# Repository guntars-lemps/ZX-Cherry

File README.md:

The ZX Cherry is a keyboard replacement for the ZX Spectrum plus membrane keyboard based on Cherry MX switches. The keyboard keeps the original look of the ZX Spectrum plus which has a much better and more durable keyboard. For extended keys, the BU4066 (or compatible) switches and other elements are used. I suggest to use brown cherry switches, they are noiseless and have tactile feedback.

To use ZX Cherry keyboard together with the original zx spectrum board, the ribbon cable connectors should be replaced with wired connectors, and additionally two power wires must be routed together with the KB0..KB4 wires to JP1 connector

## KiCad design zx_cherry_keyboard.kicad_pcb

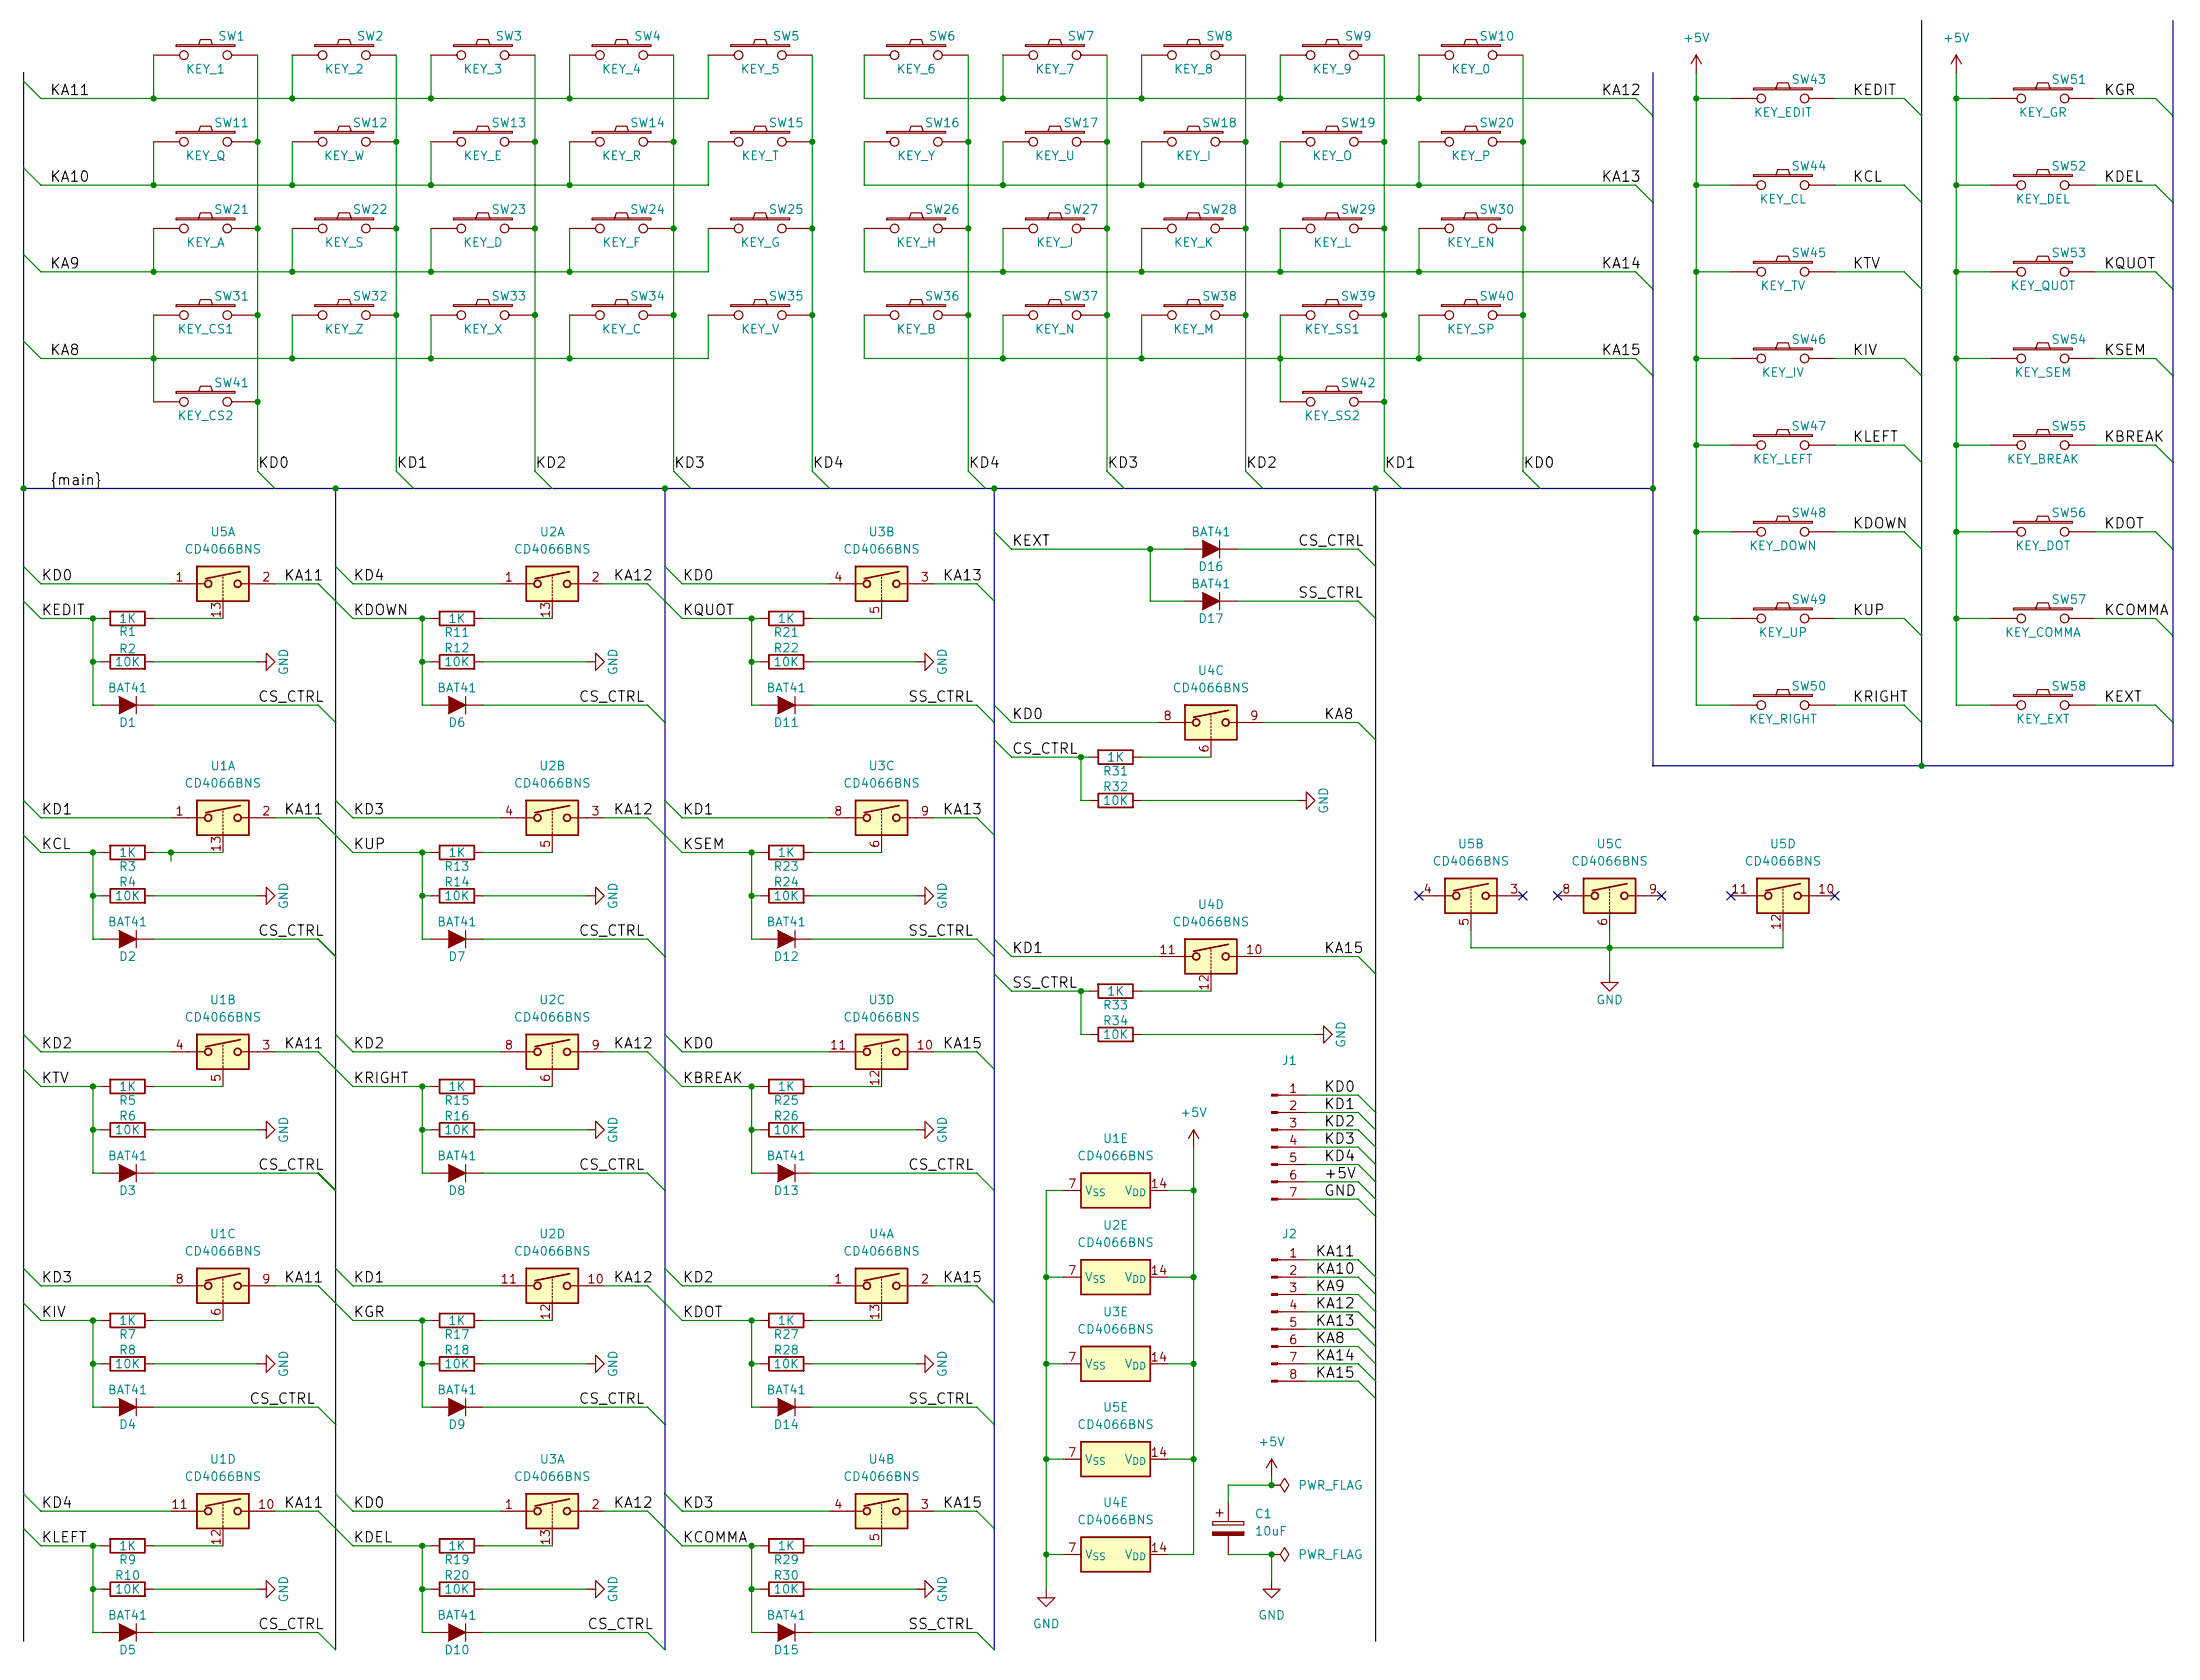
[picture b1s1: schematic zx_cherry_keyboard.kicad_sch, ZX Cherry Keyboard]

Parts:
C1: 10uF; CP_EIA-7343-43_Kemet-X_Pad2.25x2.55mm_HandSolder
D1, D2, D3, D4, D5, D6, D7, D8, D9, D10, D11, D12, D13, D14, D15, D16, D17: BAT41; D_DO-35_SOD27_P12.70mm_Horizontal
J1: Conn_01x07_Pin; PinHeader_1x07_P2.54mm_Horizontal
J2: Conn_01x08_Pin; PinHeader_1x08_P2.54mm_Horizontal
R1, R3, R5, R7, R9, R11, R13, R15, R17, R19, R21, R23, R25, R27, R29, R31, R33: 1K; R_0805_2012Metric_Pad1.20x1.40mm_HandSolder
R2, R4, R6, R8, R10, R12, R14, R16, R18, R20, R22, R24, R26, R28, R30, R32, R34: 10K; R_0805_2012Metric_Pad1.20x1.40mm_HandSolder
SW1: KEY_1; SW_Cherry_MX_1.00u_Plate
SW2: KEY_2; SW_Cherry_MX_1.00u_Plate
SW3: KEY_3; SW_Cherry_MX_1.00u_Plate
SW4: KEY_4; SW_Cherry_MX_1.00u_Plate
SW5: KEY_5; SW_Cherry_MX_1.00u_Plate
SW6: KEY_6; SW_Cherry_MX_1.00u_Plate
SW7: KEY_7; SW_Cherry_MX_1.00u_Plate
SW8: KEY_8; SW_Cherry_MX_1.00u_Plate
SW9: KEY_9; SW_Cherry_MX_1.00u_Plate
SW10: KEY_0; SW_Cherry_MX_1.00u_Plate
SW11: KEY_Q; SW_Cherry_MX_1.00u_Plate
SW12: KEY_W; SW_Cherry_MX_1.00u_Plate
SW13: KEY_E; SW_Cherry_MX_1.00u_Plate
SW14: KEY_R; SW_Cherry_MX_1.00u_Plate
SW15: KEY_T; SW_Cherry_MX_1.00u_Plate
SW16: KEY_Y; SW_Cherry_MX_1.00u_Plate
SW17: KEY_U; SW_Cherry_MX_1.00u_Plate
SW18: KEY_I; SW_Cherry_MX_1.00u_Plate
SW19: KEY_O; SW_Cherry_MX_1.00u_Plate
SW20: KEY_P; SW_Cherry_MX_1.00u_Plate
SW21: KEY_A; SW_Cherry_MX_1.00u_Plate
SW22: KEY_S; SW_Cherry_MX_1.00u_Plate
SW23: KEY_D; SW_Cherry_MX_1.00u_Plate
SW24: KEY_F; SW_Cherry_MX_1.00u_Plate
SW25: KEY_G; SW_Cherry_MX_1.00u_Plate
SW26: KEY_H; SW_Cherry_MX_1.00u_Plate
SW27: KEY_J; SW_Cherry_MX_1.00u_Plate
SW28: KEY_K; SW_Cherry_MX_1.00u_Plate
SW29: KEY_L; SW_Cherry_MX_1.00u_Plate
SW30: KEY_EN; SW_Cherry_MX_1.00u_Plate
SW31: KEY_CS1; SW_Cherry_MX_1.00u_Plate
SW32: KEY_Z; SW_Cherry_MX_1.00u_Plate
SW33: KEY_X; SW_Cherry_MX_1.00u_Plate
SW34: KEY_C; SW_Cherry_MX_1.00u_Plate
SW35: KEY_V; SW_Cherry_MX_1.00u_Plate
SW36: KEY_B; SW_Cherry_MX_1.00u_Plate
SW37: KEY_N; SW_Cherry_MX_1.00u_Plate
SW38: KEY_M; SW_Cherry_MX_1.00u_Plate
SW39: KEY_SS1; SW_Cherry_MX_1.00u_Plate
SW40: KEY_SP; SW_Cherry_MX_1.00u_Plate
SW41: KEY_CS2; SW_Cherry_MX_1.00u_Plate
SW42: KEY_SS2; SW_Cherry_MX_1.00u_Plate
SW43: KEY_EDIT; SW_Cherry_MX_1.00u_Plate
SW44: KEY_CL; SW_Cherry_MX_1.00u_Plate
SW45: KEY_TV; SW_Cherry_MX_1.00u_Plate
SW46: KEY_IV; SW_Cherry_MX_1.00u_Plate
SW47: KEY_LEFT; SW_Cherry_MX_1.00u_Plate
SW48: KEY_DOWN; SW_Cherry_MX_1.00u_Plate
SW49: KEY_UP; SW_Cherry_MX_1.00u_Plate
SW50: KEY_RIGHT; SW_Cherry_MX_1.00u_Plate
SW51: KEY_GR; SW_Cherry_MX_1.00u_Plate
SW52: KEY_DEL; SW_Cherry_MX_1.00u_Plate
SW53: KEY_QUOT; SW_Cherry_MX_1.00u_Plate
SW54: KEY_SEM; SW_Cherry_MX_1.00u_Plate
SW55: KEY_BREAK; SW_Cherry_MX_1.00u_Plate
SW56: KEY_DOT; SW_Cherry_MX_1.00u_Plate
SW57: KEY_COMMA; SW_Cherry_MX_1.00u_Plate
SW58: KEY_EXT; SW_Cherry_MX_1.00u_Plate
U1, U2, U3, U4, U5: CD4066BNS; SO-14_5.3x10.2mm_P1.27mm

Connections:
+5V: C1.1, J1.6, SW43.1, SW44.1, SW45.1, SW46.1, SW47.1, SW48.1, SW49.1, SW50.1, SW51.1, SW52.1, SW53.1, SW54.1, SW55.1, SW56.1, SW57.1, SW58.1, U1.14 (V_{DD}), U2.14 (V_{DD}), U3.14 (V_{DD}), U4.14 (V_{DD}), U5.14 (V_{DD})
/CS_CTRL: D1.1 (K), D2.1 (K), D3.1 (K), D4.1 (K), D5.1 (K), D6.1 (K), D7.1 (K), D8.1 (K), D9.1 (K), D10.1 (K), D13.1 (K), D16.1 (K), R31.2, R32.1
/KA8: J2.6, SW31.1, SW32.1, SW33.1, SW34.1, SW35.1, SW41.1, U4.9
/KA9: J2.3, SW21.1, SW22.1, SW23.1, SW24.1, SW25.1
/KA10: J2.2, SW11.1, SW12.1, SW13.1, SW14.1, SW15.1
/KA11: J2.1, SW1.1, SW2.1, SW3.1, SW4.1, SW5.1, U1.2, U1.3, U1.9, U1.10, U5.2
/KA12: J2.4, SW6.1, SW7.1, SW8.1, SW9.1, SW10.1, U2.2, U2.3, U2.9, U2.10, U3.2
/KA13: J2.5, SW16.1, SW17.1, SW18.1, SW19.1, SW20.1, U3.3, U3.9
/KA14: J2.7, SW26.1, SW27.1, SW28.1, SW29.1, SW30.1
/KA15: J2.8, SW36.1, SW37.1, SW38.1, SW39.1, SW40.1, SW42.1, U3.10, U4.2, U4.3, U4.10
/KBREAK: D13.2 (A), R25.2, R26.1, SW55.2
/KCL: D2.2 (A), R3.2, R4.1, SW44.2
/KCOMMA: D15.2 (A), R29.2, R30.1, SW57.2
/KD0: J1.1, SW1.2, SW10.2, SW11.2, SW20.2, SW21.2, SW30.2, SW31.2, SW40.2, SW41.2, U3.1, U3.4, U3.11, U4.8, U5.1
/KD1: J1.2, SW2.2, SW9.2, SW12.2, SW19.2, SW22.2, SW29.2, SW32.2, SW39.2, SW42.2, U1.1, U2.11, U3.8, U4.11
/KD2: J1.3, SW3.2, SW8.2, SW13.2, SW18.2, SW23.2, SW28.2, SW33.2, SW38.2, U1.4, U2.8, U4.1
/KD3: J1.4, SW4.2, SW7.2, SW14.2, SW17.2, SW24.2, SW27.2, SW34.2, SW37.2, U1.8, U2.4, U4.4
/KD4: J1.5, SW5.2, SW6.2, SW15.2, SW16.2, SW25.2, SW26.2, SW35.2, SW36.2, U1.11, U2.1
/KDEL: D10.2 (A), R19.2, R20.1, SW52.2
/KDOT: D14.2 (A), R27.2, R28.1, SW56.2
/KDOWN: D6.2 (A), R11.2, R12.1, SW48.2
/KEDIT: D1.2 (A), R1.2, R2.1, SW43.2
/KEXT: D16.2 (A), D17.2 (A), SW58.2
/KGR: D9.2 (A), R17.2, R18.1, SW51.2
/KIV: D4.2 (A), R7.2, R8.1, SW46.2
/KLEFT: D5.2 (A), R9.2, R10.1, SW47.2
/KQUOT: D11.2 (A), R21.2, R22.1, SW53.2
/KRIGHT: D8.2 (A), R15.2, R16.1, SW50.2
/KSEM: D12.2 (A), R23.2, R24.1, SW54.2
/KTV: D3.2 (A), R5.2, R6.1, SW45.2
/KUP: D7.2 (A), R13.2, R14.1, SW49.2
/SS_CTRL: D11.1 (K), D12.1 (K), D14.1 (K), D15.1 (K), D17.1 (K), R33.2, R34.1
GND: C1.2, J1.7, R2.2, R4.2, R6.2, R8.2, R10.2, R12.2, R14.2, R16.2, R18.2, R20.2, R22.2, R24.2, R26.2, R28.2, R30.2, R32.2, R34.2, U1.7 (V_{SS}), U2.7 (V_{SS}), U3.7 (V_{SS}), U4.7 (V_{SS}), U5.5, U5.6, U5.7 (V_{SS}), U5.12
unnamed: R1.1, U5.13
unnamed: R3.1, U1.13
unnamed: R5.1, U1.5
unnamed: R7.1, U1.6
unnamed: R9.1, U1.12
unnamed: R11.1, U2.13
unnamed: R13.1, U2.5
unnamed: R15.1, U2.6
unnamed: R17.1, U2.12
unnamed: R19.1, U3.13
unnamed: R21.1, U3.5
unnamed: R23.1, U3.6
unnamed: R25.1, U3.12
unnamed: R27.1, U4.13
unnamed: R29.1, U4.5
unnamed: R31.1, U4.6
unnamed: R33.1, U4.12

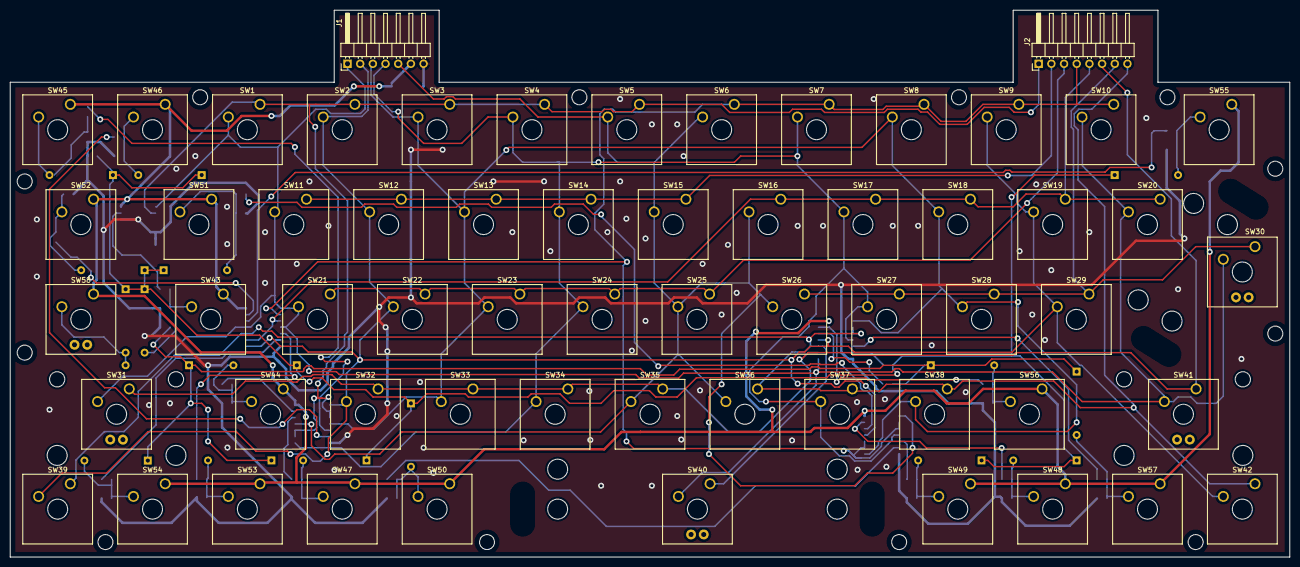
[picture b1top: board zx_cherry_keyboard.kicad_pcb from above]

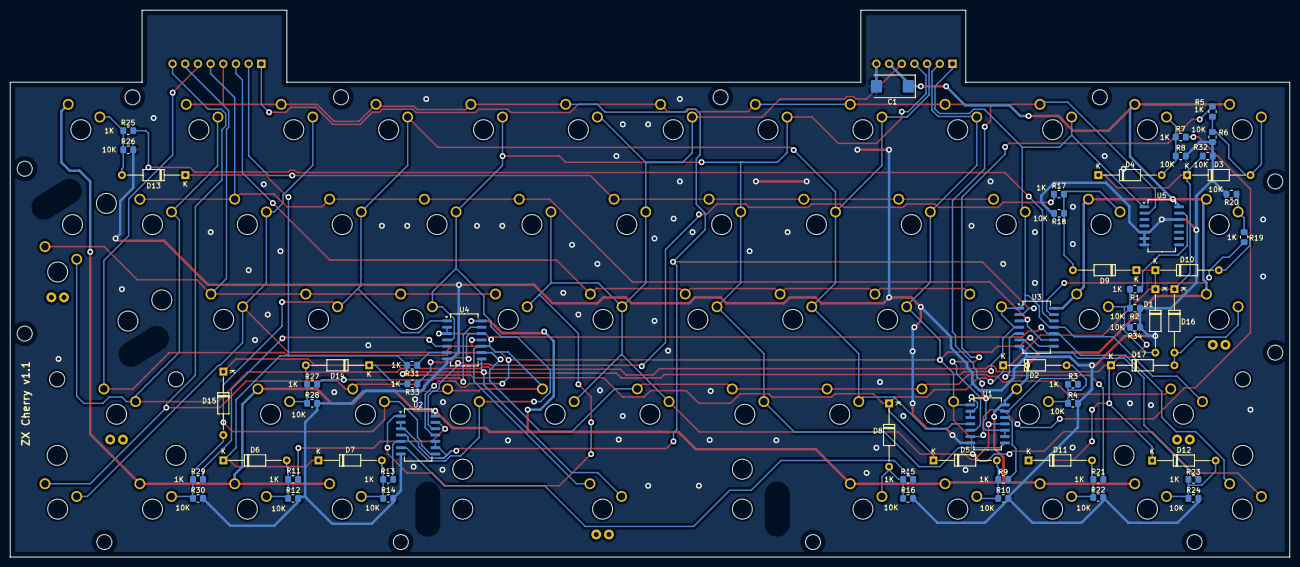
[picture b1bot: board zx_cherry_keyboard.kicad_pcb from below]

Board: 2 copper layers, 256.3 x 109.5 mm, 117 parts (57 on the bottom side), 50 nets.

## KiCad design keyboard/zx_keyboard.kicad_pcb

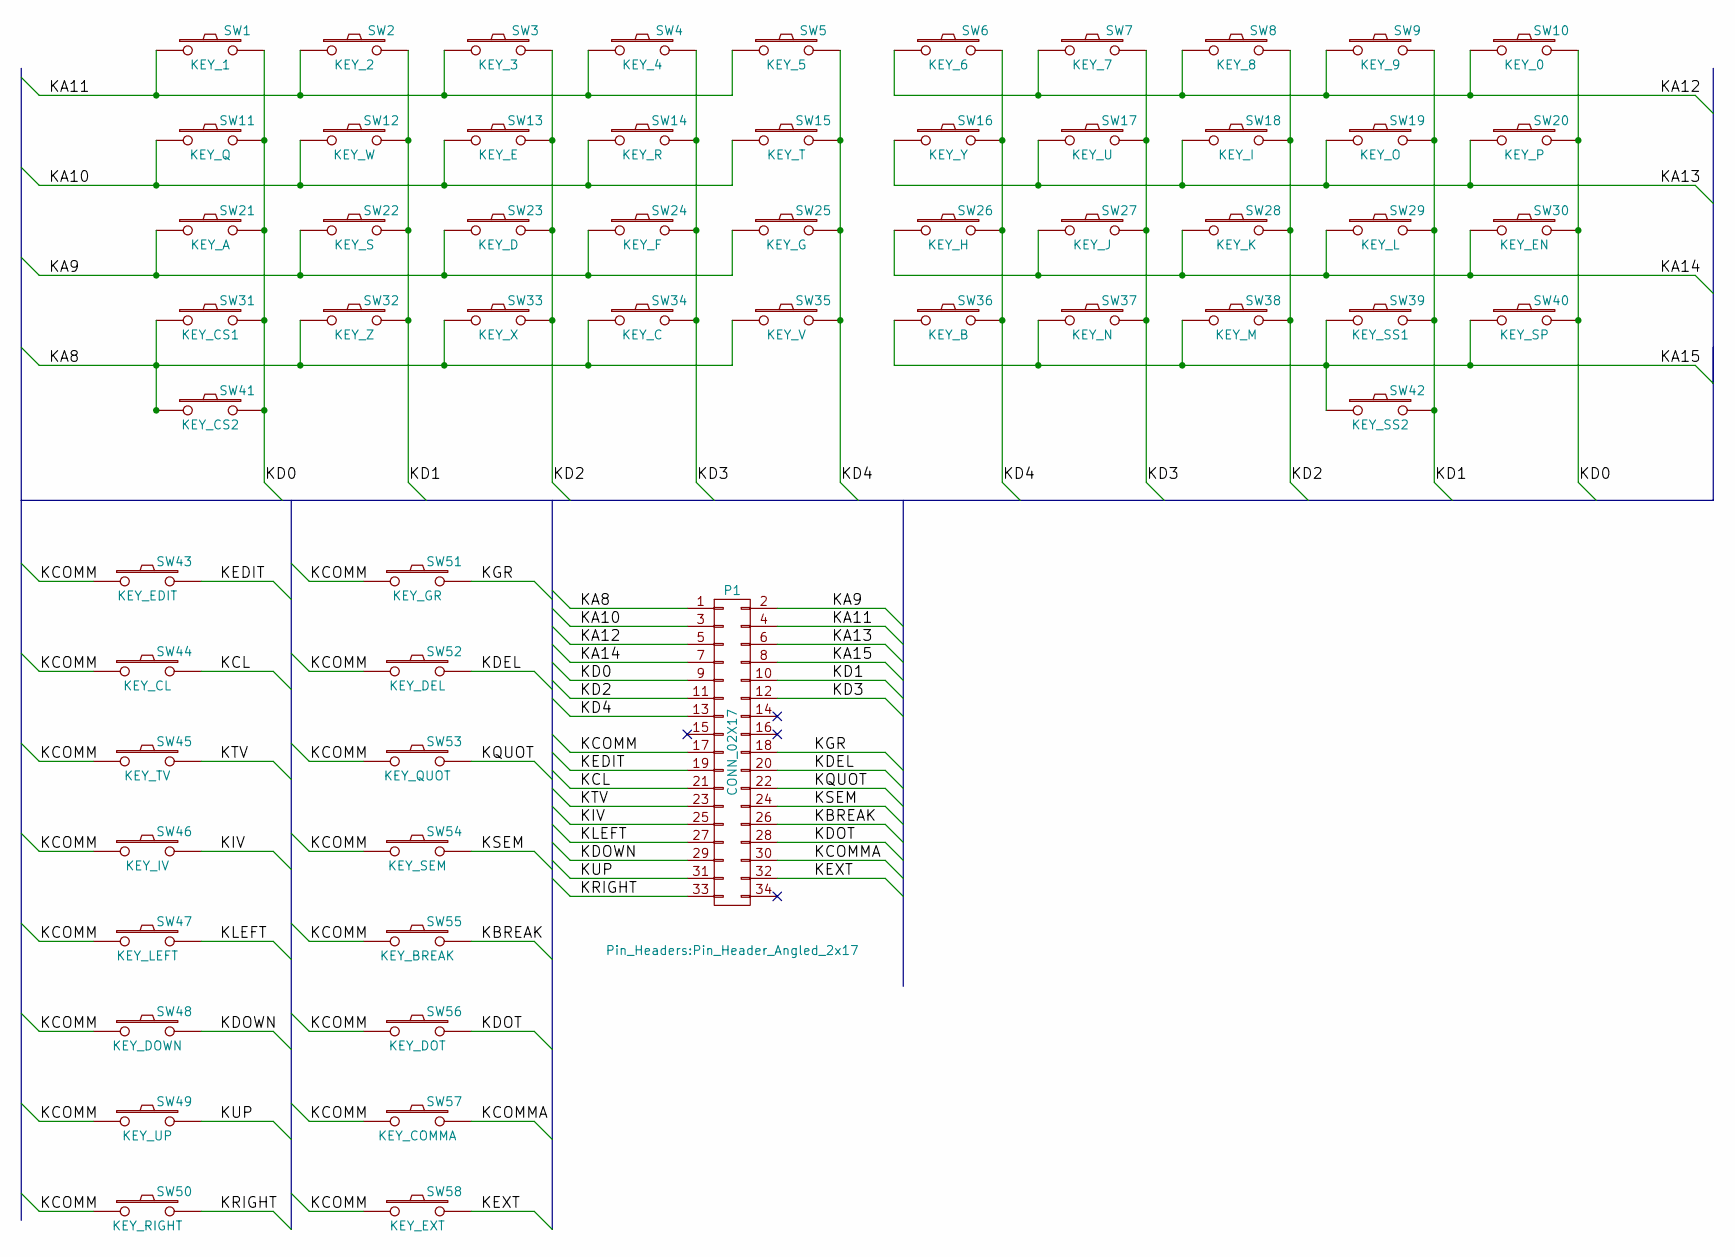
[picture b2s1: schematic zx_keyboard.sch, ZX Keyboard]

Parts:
P1: CONN_02X17; Pin_Header_Angled_2x17
SW1: KEY_1; SW_Cherry_MX1A_1.00u_PCB
SW2: KEY_2; SW_Cherry_MX1A_1.00u_PCB
SW3: KEY_3; SW_Cherry_MX1A_1.00u_PCB
SW4: KEY_4; SW_Cherry_MX1A_1.00u_PCB
SW5: KEY_5; SW_Cherry_MX1A_1.00u_PCB
SW6: KEY_6; SW_Cherry_MX1A_1.00u_PCB
SW7: KEY_7; SW_Cherry_MX1A_1.00u_PCB
SW8: KEY_8; SW_Cherry_MX1A_1.00u_PCB
SW9: KEY_9; SW_Cherry_MX1A_1.00u_PCB
SW10: KEY_0; SW_Cherry_MX1A_1.00u_PCB
SW11: KEY_Q; SW_Cherry_MX1A_1.00u_PCB
SW12: KEY_W; SW_Cherry_MX1A_1.00u_PCB
SW13: KEY_E; SW_Cherry_MX1A_1.00u_PCB
SW14: KEY_R; SW_Cherry_MX1A_1.00u_PCB
SW15: KEY_T; SW_Cherry_MX1A_1.00u_PCB
SW16: KEY_Y; SW_Cherry_MX1A_1.00u_PCB
SW17: KEY_U; SW_Cherry_MX1A_1.00u_PCB
SW18: KEY_I; SW_Cherry_MX1A_1.00u_PCB
SW19: KEY_O; SW_Cherry_MX1A_1.00u_PCB
SW20: KEY_P; SW_Cherry_MX1A_1.00u_PCB
SW21: KEY_A; SW_Cherry_MX1A_1.00u_PCB
SW22: KEY_S; SW_Cherry_MX1A_1.00u_PCB
SW23: KEY_D; SW_Cherry_MX1A_1.00u_PCB
SW24: KEY_F; SW_Cherry_MX1A_1.00u_PCB
SW25: KEY_G; SW_Cherry_MX1A_1.00u_PCB
SW26: KEY_H; SW_Cherry_MX1A_1.00u_PCB
SW27: KEY_J; SW_Cherry_MX1A_1.00u_PCB
SW28: KEY_K; SW_Cherry_MX1A_1.00u_PCB
SW29: KEY_L; SW_Cherry_MX1A_1.00u_PCB
SW30: KEY_EN; SW_Cherry_MX1A_1.00u_PCB
SW31: KEY_CS1; SW_Cherry_MX1A_1.00u_PCB
SW32: KEY_Z; SW_Cherry_MX1A_1.00u_PCB
SW33: KEY_X; SW_Cherry_MX1A_1.00u_PCB
SW34: KEY_C; SW_Cherry_MX1A_1.00u_PCB
SW35: KEY_V; SW_Cherry_MX1A_1.00u_PCB
SW36: KEY_B; SW_Cherry_MX1A_1.00u_PCB
SW37: KEY_N; SW_Cherry_MX1A_1.00u_PCB
SW38: KEY_M; SW_Cherry_MX1A_1.00u_PCB
SW39: KEY_SS1; SW_Cherry_MX1A_1.00u_PCB
SW40: KEY_SP; SW_Cherry_MX1A_1.00u_PCB
SW41: KEY_CS2; SW_Cherry_MX1A_1.00u_PCB
SW42: KEY_SS2; SW_Cherry_MX1A_1.00u_PCB
SW43: KEY_EDIT; SW_Cherry_MX1A_1.00u_PCB
SW44: KEY_CL; SW_Cherry_MX1A_1.00u_PCB
SW45: KEY_TV; SW_Cherry_MX1A_1.00u_PCB
SW46: KEY_IV; SW_Cherry_MX1A_1.00u_PCB
SW47: KEY_LEFT; SW_Cherry_MX1A_1.00u_PCB
SW48: KEY_DOWN; SW_Cherry_MX1A_1.00u_PCB
SW49: KEY_UP; SW_Cherry_MX1A_1.00u_PCB
SW50: KEY_RIGHT; SW_Cherry_MX1A_1.00u_PCB
SW51: KEY_GR; SW_Cherry_MX1A_1.00u_PCB
SW52: KEY_DEL; SW_Cherry_MX1A_1.00u_PCB
SW53: KEY_QUOT; SW_Cherry_MX1A_1.00u_PCB
SW54: KEY_SEM; SW_Cherry_MX1A_1.00u_PCB
SW55: KEY_BREAK; SW_Cherry_MX1A_1.00u_PCB
SW56: KEY_DOT; SW_Cherry_MX1A_1.00u_PCB
SW57: KEY_COMMA; SW_Cherry_MX1A_1.00u_PCB
SW58: KEY_EXT; SW_Cherry_MX1A_1.00u_PCB

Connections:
/KA8: P1.1, SW31.1, SW32.1, SW33.1, SW34.1, SW35.1, SW41.1
/KA9: P1.2, SW21.1, SW22.1, SW23.1, SW24.1, SW25.1
/KA10: P1.3, SW11.1, SW12.1, SW13.1, SW14.1, SW15.1
/KA11: P1.4, SW1.1, SW2.1, SW3.1, SW4.1, SW5.1
/KA12: P1.5, SW6.1, SW7.1, SW8.1, SW9.1, SW10.1
/KA13: P1.6, SW16.1, SW17.1, SW18.1, SW19.1, SW20.1
/KA14: P1.7, SW26.1, SW27.1, SW28.1, SW29.1, SW30.1
/KA15: P1.8, SW36.1, SW37.1, SW38.1, SW39.1, SW40.1, SW42.1
/KBREAK: P1.26, SW55.2
/KCL: P1.21, SW44.2
/KCOMM: P1.17, SW43.1, SW44.1, SW45.1, SW46.1, SW47.1, SW48.1, SW49.1, SW50.1, SW51.1, SW52.1, SW53.1, SW54.1, SW55.1, SW56.1, SW57.1, SW58.1
/KCOMMA: P1.30, SW57.2
/KD0: P1.9, SW1.2, SW10.2, SW11.2, SW20.2, SW21.2, SW30.2, SW31.2, SW40.2, SW41.2
/KD1: P1.10, SW2.2, SW9.2, SW12.2, SW19.2, SW22.2, SW29.2, SW32.2, SW39.2, SW42.2
/KD2: P1.11, SW3.2, SW8.2, SW13.2, SW18.2, SW23.2, SW28.2, SW33.2, SW38.2
/KD3: P1.12, SW4.2, SW7.2, SW14.2, SW17.2, SW24.2, SW27.2, SW34.2, SW37.2
/KD4: P1.13, SW5.2, SW6.2, SW15.2, SW16.2, SW25.2, SW26.2, SW35.2, SW36.2
/KDEL: P1.20, SW52.2
/KDOT: P1.28, SW56.2
/KDOWN: P1.29, SW48.2
/KEDIT: P1.19, SW43.2
/KEXT: P1.32, SW58.2
/KGR: P1.18, SW51.2
/KIV: P1.25, SW46.2
/KLEFT: P1.27, SW47.2
/KQUOT: P1.22, SW53.2
/KRIGHT: P1.33, SW50.2
/KSEM: P1.24, SW54.2
/KTV: P1.23, SW45.2
/KUP: P1.31, SW49.2

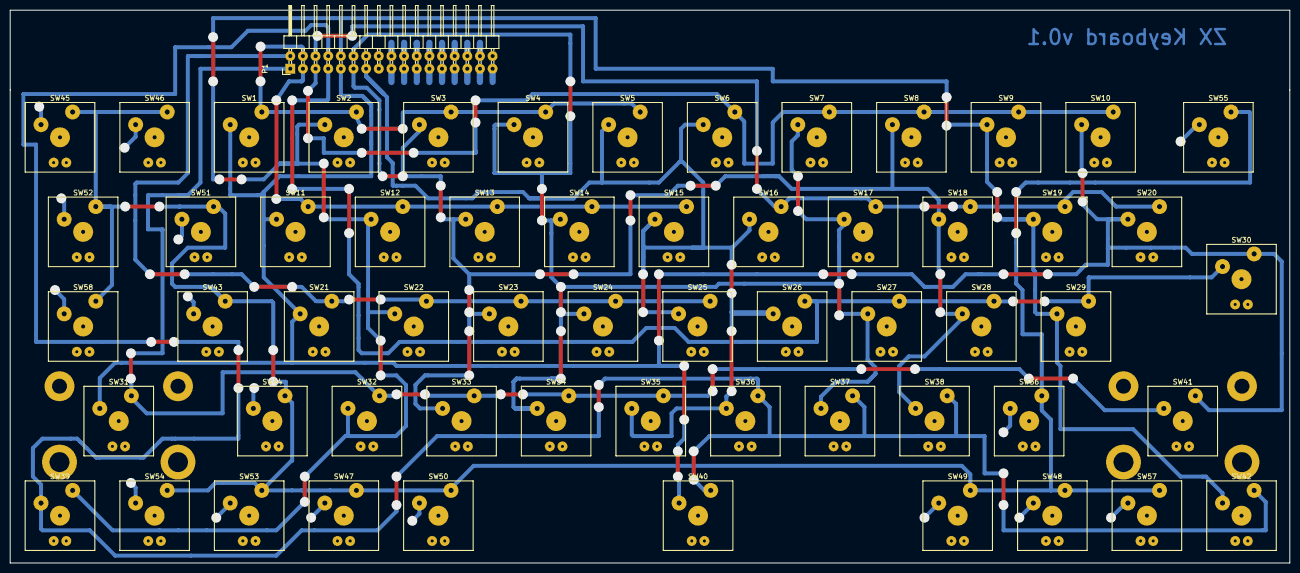
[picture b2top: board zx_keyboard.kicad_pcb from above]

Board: 2 copper layers, 257.0 x 111.0 mm, 59 parts (0 on the bottom side), 30 nets.

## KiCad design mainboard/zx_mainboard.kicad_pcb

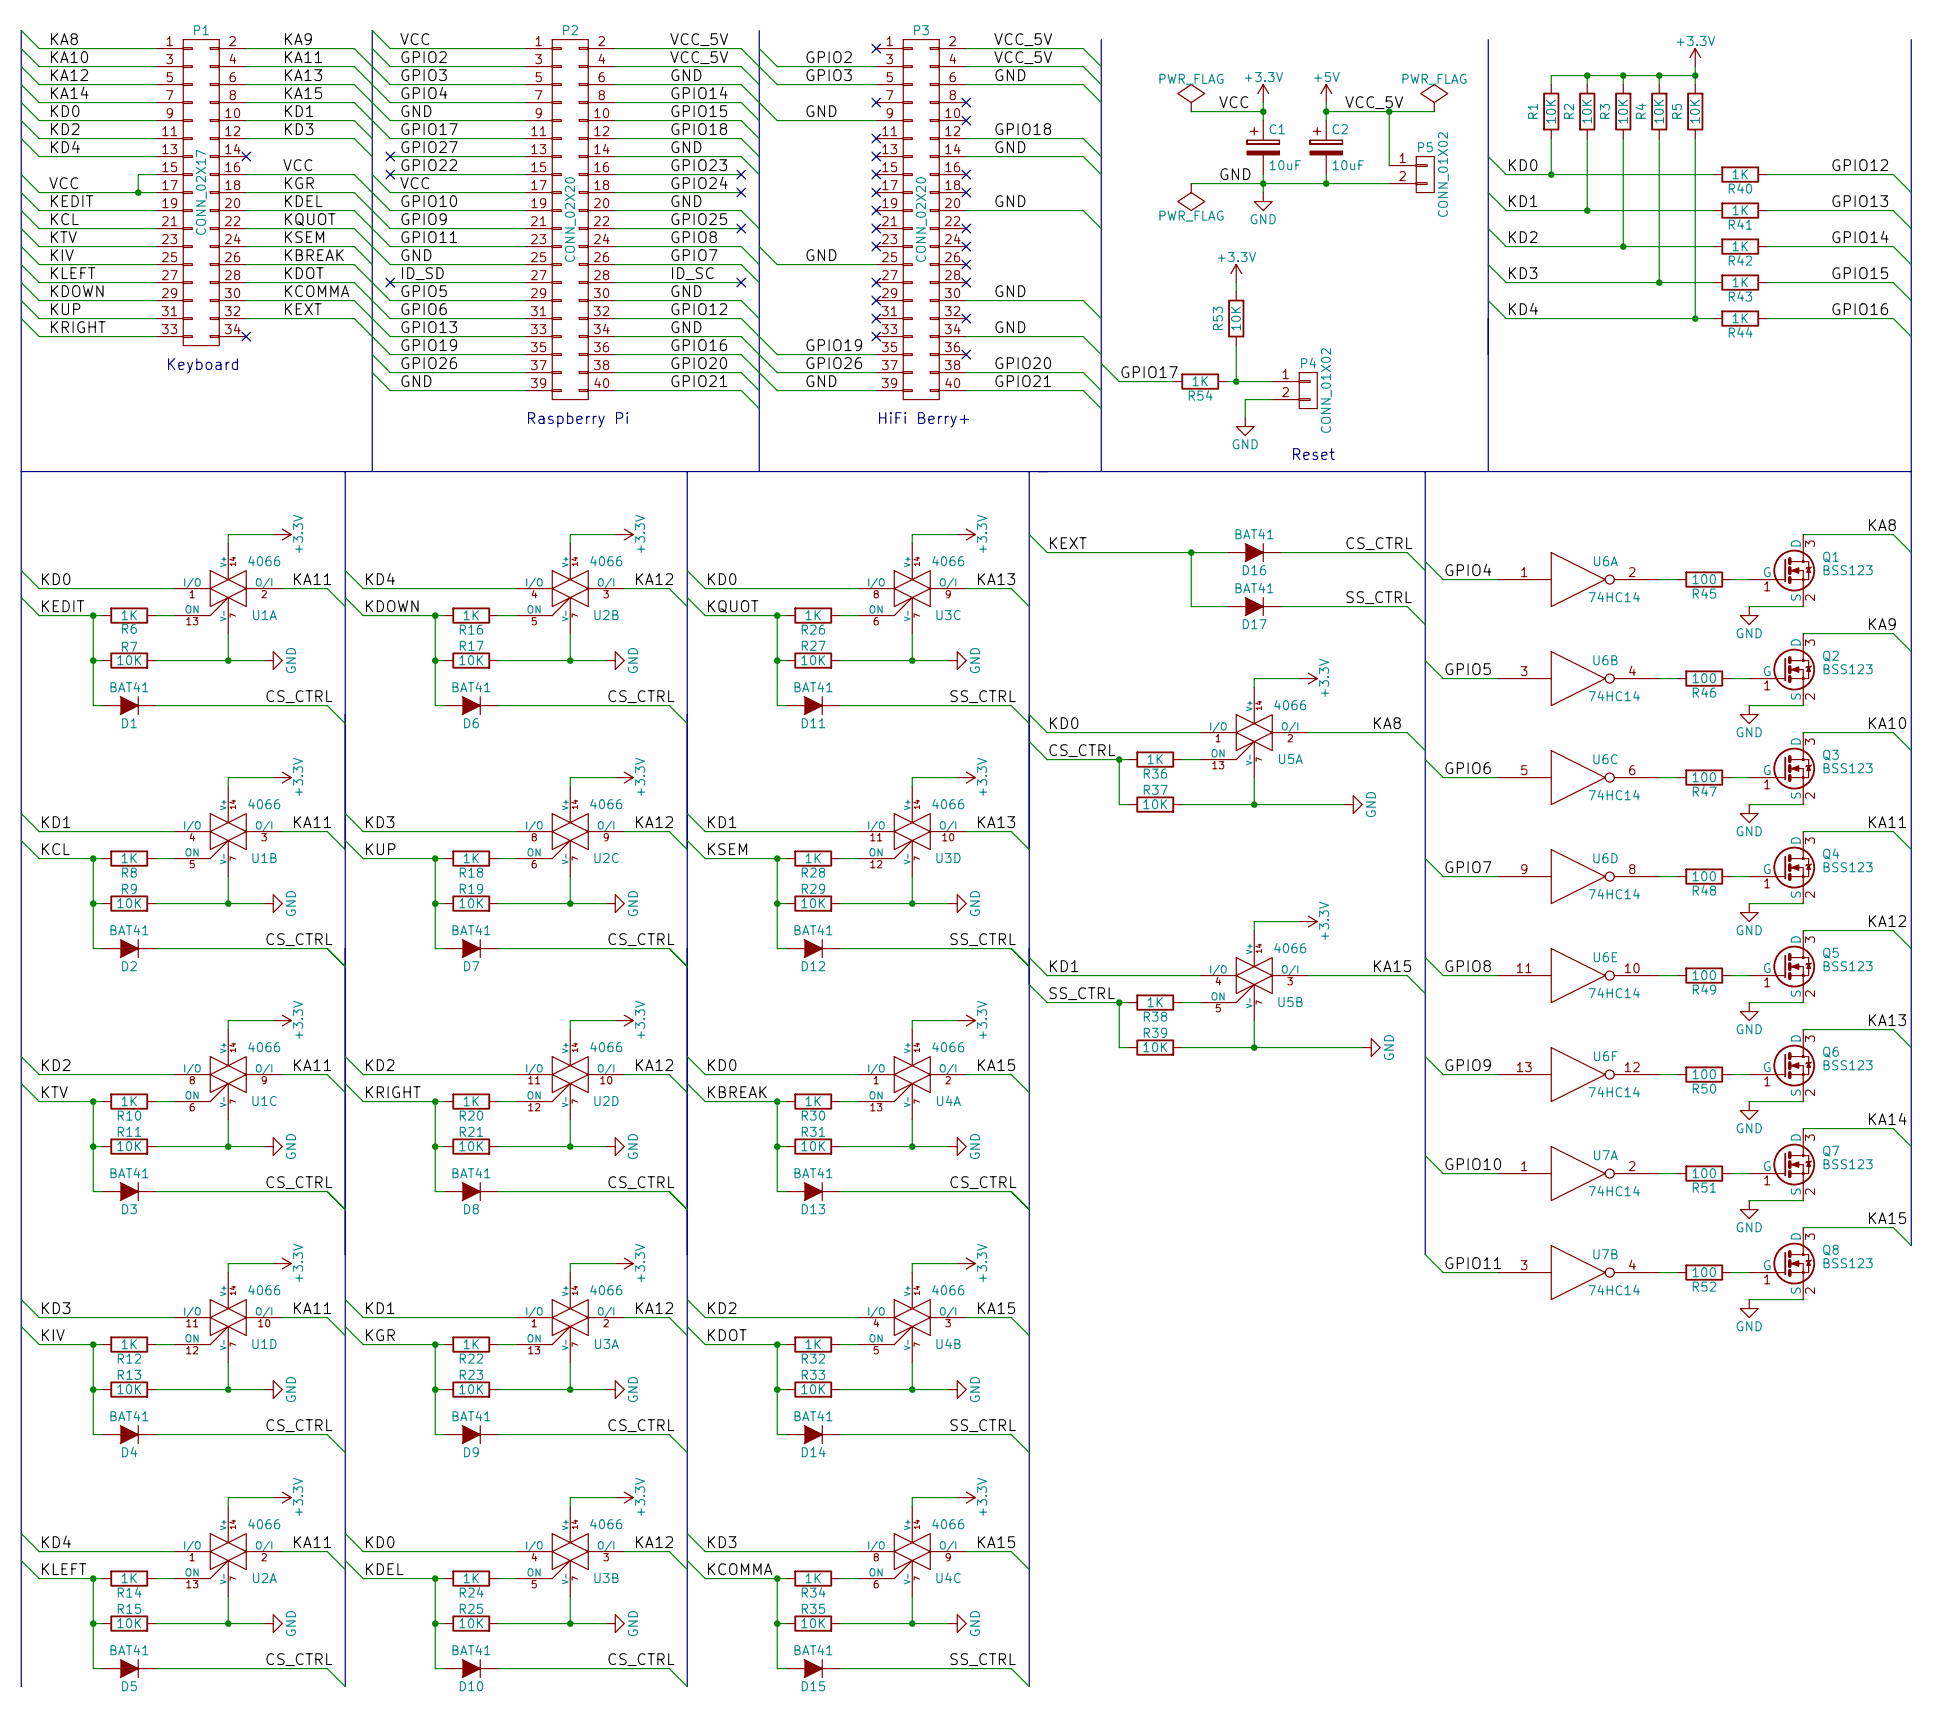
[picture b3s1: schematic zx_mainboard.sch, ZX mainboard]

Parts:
C1, C2: 10uF; TantalC_SizeC_EIA-6032_HandSoldering
D1, D2, D3, D4, D5, D6, D7, D8, D9, D10, D11, D12, D13, D14, D15, D16, D17: BAT41; Diode_DO-35_SOD27_Horizontal_RM10
P1: CONN_02X17; Pin_Header_Angled_2x17
P2, P3: CONN_02X20; Pin_Header_Angled_2x20
P4: CONN_01X02; Pin_Header_Angled_1x02
P5: CONN_01X02; PhoenixContact_MCV-G_02x5.08mm_Vertical
Q1, Q2, Q3, Q4, Q5, Q6, Q7, Q8: BSS123; SOT-23
R1, R2, R3, R4, R5, R7, R9, R11, R13, R15, R17, R19, R21, R23, R25, R27, R29, R31, R33, R35, R37, R39, R53: 10K; R_0805_HandSoldering
R6, R8, R10, R12, R14, R16, R18, R20, R22, R24, R26, R28, R30, R32, R34, R36, R38, R40, R41, R42, R43, R44, R54: 1K; R_0805_HandSoldering
R45, R46, R47, R48, R49, R50, R51, R52: 100; R_0805_HandSoldering
U1, U2, U3, U4, U5: 4066; TSSOP-14_4.4x5mm_Pitch0.65mm
U6, U7: 74HC14; SOIC-14_3.9x8.7mm_Pitch1.27mm

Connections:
+3V3: C1.1, P1.15, P1.16, P1.17, P2.1, P2.17, R1.1, R2.1, R3.2, R4.2, R5.2, R53.2, U1.14 (V+), U2.14 (V+), U3.14 (V+), U4.14 (V+), U5.14 (V+), U6.14 (VCC), U7.14 (VCC)
+5V: C2.1, P2.2, P2.4, P3.2, P3.4, P5.1
/CS_CTRL: D1.1 (K), D2.1 (K), D3.1 (K), D4.1 (K), D5.1 (K), D6.1 (K), D7.1 (K), D8.1 (K), D9.1 (K), D10.1 (K), D13.1 (K), D16.1 (K), R36.2, R37.1
/GPIO2: P2.3, P3.3
/GPIO3: P2.5, P3.5
/GPIO4: P2.7, U6.1
/GPIO5: P2.29, U6.3
/GPIO6: P2.31, U6.5
/GPIO7: P2.26, U6.9
/GPIO8: P2.24, U6.11
/GPIO9: P2.21, U6.13
/GPIO10: P2.19, U7.1
/GPIO11: P2.23, U7.3
/GPIO12: P2.32, R40.1
/GPIO13: P2.33, R41.1
/GPIO14: P2.8, R42.1
/GPIO15: P2.10, R43.1
/GPIO16: P2.36, R44.1
/GPIO17: P2.11, R54.2
/GPIO18: P2.12, P3.12
/GPIO19: P2.35, P3.35
/GPIO20: P2.38, P3.38
/GPIO21: P2.40, P3.40
/GPIO22: P2.15
/GPIO23: P2.16
/GPIO24: P2.18
/GPIO25: P2.22
/GPIO26: P2.37, P3.37
/GPIO27: P2.13
/ID_SC: P2.28
/ID_SD: P2.27
/KA8: P1.1, Q1.3 (D), U5.2 (O/I)
/KA9: P1.2, Q2.3 (D)
/KA10: P1.3, Q3.3 (D)
/KA11: P1.4, Q4.3 (D), U1.2 (O/I), U1.3 (O/I), U1.9 (O/I), U1.10 (O/I), U2.2 (O/I)
/KA12: P1.5, Q5.3 (D), U2.3 (O/I), U2.9 (O/I), U2.10 (O/I), U3.2 (O/I), U3.3 (O/I)
/KA13: P1.6, Q6.3 (D), U3.9 (O/I), U3.10 (O/I)
/KA14: P1.7, Q7.3 (D)
/KA15: P1.8, Q8.3 (D), U4.2 (O/I), U4.3 (O/I), U4.9 (O/I), U5.3 (O/I)
/KBREAK: D13.2 (A), P1.26, R30.2, R31.1
/KCL: D2.2 (A), P1.21, R8.2, R9.1
/KCOMMA: D15.2 (A), P1.30, R34.2, R35.1
/KD0: P1.9, R1.2, R40.2, U1.1 (I/O), U3.4 (I/O), U3.8 (I/O), U4.1 (I/O), U5.1 (I/O)
/KD1: P1.10, R2.2, R41.2, U1.4 (I/O), U3.1 (I/O), U3.11 (I/O), U5.4 (I/O)
/KD2: P1.11, R3.1, R42.2, U1.8 (I/O), U2.11 (I/O), U4.4 (I/O)
/KD3: P1.12, R4.1, R43.2, U1.11 (I/O), U2.8 (I/O), U4.8 (I/O)
/KD4: P1.13, R5.1, R44.2, U2.1 (I/O), U2.4 (I/O)
/KDEL: D10.2 (A), P1.20, R24.2, R25.1
/KDOT: D14.2 (A), P1.28, R32.2, R33.1
/KDOWN: D6.2 (A), P1.29, R16.2, R17.1
/KEDIT: D1.2 (A), P1.19, R6.2, R7.1
/KEXT: D16.2 (A), D17.2 (A), P1.32
/KGR: D9.2 (A), P1.18, R22.2, R23.1
/KIV: D4.2 (A), P1.25, R12.2, R13.1
/KLEFT: D5.2 (A), P1.27, R14.2, R15.1
/KQUOT: D11.2 (A), P1.22, R26.2, R27.1
/KRIGHT: D8.2 (A), P1.33, R20.2, R21.1
/KSEM: D12.2 (A), P1.24, R28.2, R29.1
/KTV: D3.2 (A), P1.23, R10.2, R11.1
/KUP: D7.2 (A), P1.31, R18.2, R19.1
/SS_CTRL: D11.1 (K), D12.1 (K), D14.1 (K), D15.1 (K), D17.1 (K), R38.2, R39.1
GND: C1.2, C2.2, P2.6, P2.9, P2.14, P2.20, P2.25, P2.30, P2.34, P2.39, P3.6, P3.9, P3.14, P3.20, P3.25, P3.30, P3.34, P3.39, P4.2, P5.2, Q1.2 (S), Q2.2 (S), Q3.2 (S), Q4.2 (S), Q5.2 (S), Q6.2 (S), Q7.2 (S), Q8.2 (S), R7.2, R9.2, R11.2, R13.2, R15.2, R17.2, R19.2, R21.2, R23.2, R25.2, R27.2, R29.2, R31.2, R33.2, R35.2, R37.2, R39.2, U1.7 (V-), U2.7 (V-), U3.7 (V-), U4.7 (V-), U5.7 (V-), U6.7 (GND), U7.7 (GND)
unnamed: P4.1, R53.1, R54.1
unnamed: Q1.1 (G), R45.1
unnamed: Q2.1 (G), R46.1
unnamed: Q3.1 (G), R47.1
unnamed: Q4.1 (G), R48.1
unnamed: Q5.1 (G), R49.1
unnamed: Q6.1 (G), R50.1
unnamed: Q7.1 (G), R51.1
unnamed: Q8.1 (G), R52.1
unnamed: R6.1, U1.13 (ON)
unnamed: R8.1, U1.5 (ON)
unnamed: R10.1, U1.6 (ON)
unnamed: R12.1, U1.12 (ON)
unnamed: R14.1, U2.13 (ON)
unnamed: R16.1, U2.5 (ON)
unnamed: R18.1, U2.6 (ON)
unnamed: R20.1, U2.12 (ON)
unnamed: R22.1, U3.13 (ON)
unnamed: R24.1, U3.5 (ON)
unnamed: R26.1, U3.6 (ON)
unnamed: R28.1, U3.12 (ON)
unnamed: R30.1, U4.13 (ON)
unnamed: R32.1, U4.5 (ON)
unnamed: R34.1, U4.6 (ON)
unnamed: R36.1, U5.13 (ON)
unnamed: R38.1, U5.5 (ON)
unnamed: R45.2, U6.2
unnamed: R46.2, U6.4
unnamed: R47.2, U6.6
unnamed: R48.2, U6.8
unnamed: R49.2, U6.10
unnamed: R50.2, U6.12
unnamed: R51.2, U7.2
unnamed: R52.2, U7.4

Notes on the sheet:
HiFi Berry+
Raspberry Pi
Keyboard
Reset

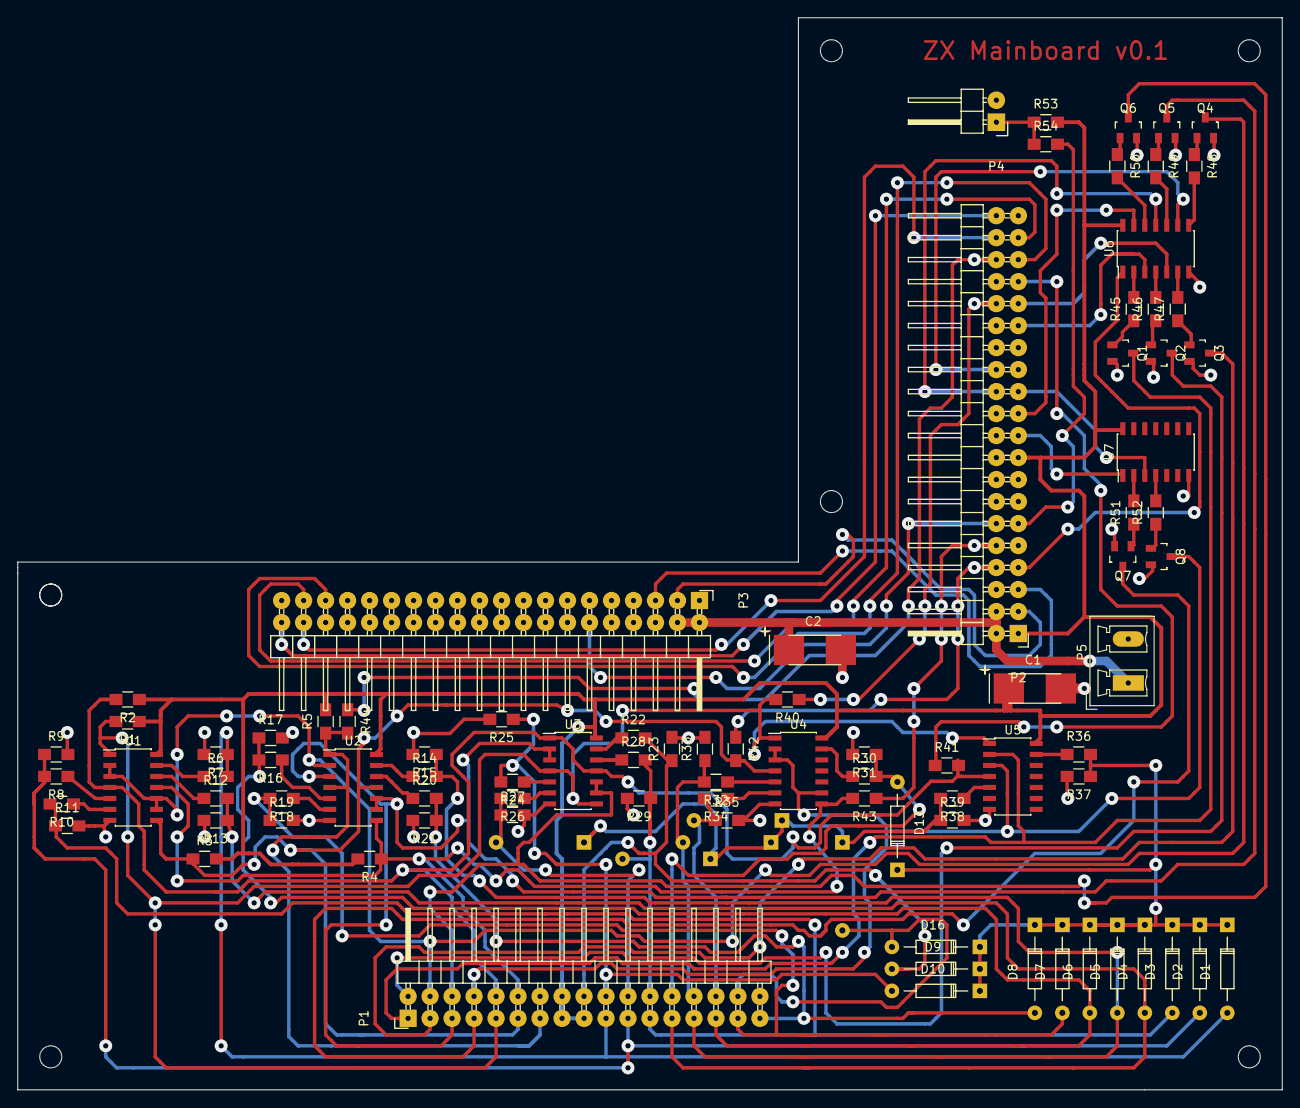
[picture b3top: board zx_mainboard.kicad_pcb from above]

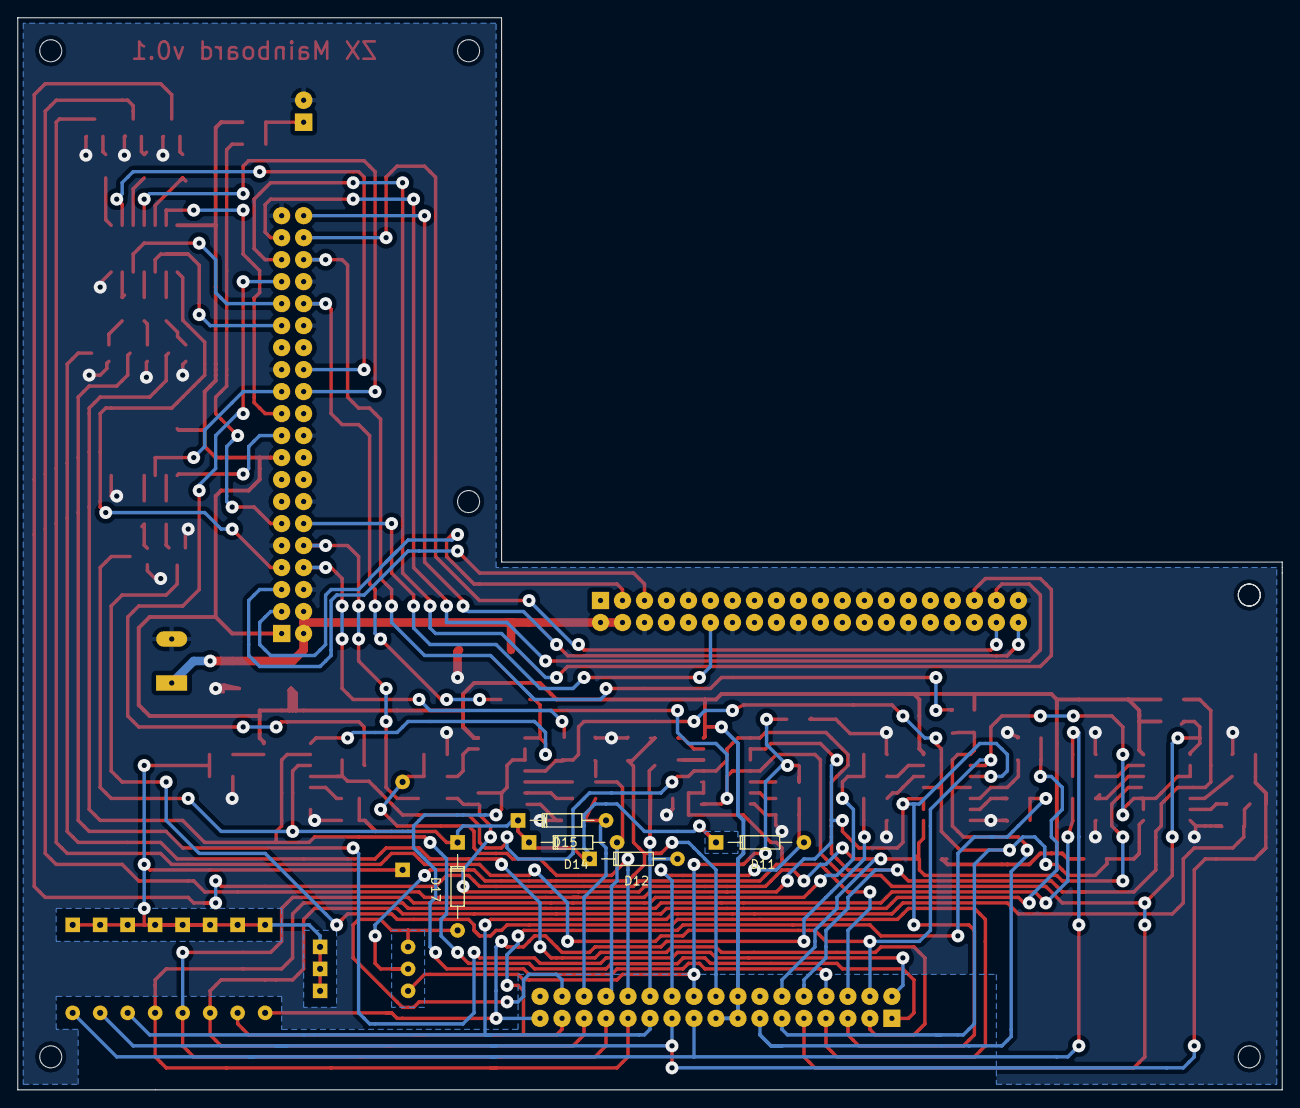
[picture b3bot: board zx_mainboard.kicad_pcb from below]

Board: 2 copper layers, 146.1 x 123.8 mm, 93 parts (5 on the bottom side), 89 nets.

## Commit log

2018-05-18 split
2018-05-30 mainboard schematics & pcb
2018-05-31 mainboard pcb
2018-06-13 keyboard pcb
2018-07-28 TV<->IV fix
2024-06-14 rev1.1 release
